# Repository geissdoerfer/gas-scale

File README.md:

# DuoClean Energy - IoT Sensor Monitoring Platform

## Project Status

✅ **Phase 1: Database Setup** - Complete
✅ **Phase 2: MQTT Ingestor** - Complete
✅ **Phase 3: Web API** - Complete
✅ **Phase 4: Web Frontend** - Complete

## What's Been Implemented

### Database (PostgreSQL + TimescaleDB)
- Complete schema with users, devices, user_device_access, sensor_readings
- TimescaleDB hypertable for sensor_readings
- Continuous aggregate for hourly statistics
- Data retention policy (1 year)
- Default admin user created
- Full init.sql script: [database/init.sql](database/init.sql)

### MQTT Ingestor Service
- MQTT client with paho-mqtt
- Database writer with connection pooling
- Auto-device registration
- Message validation
- Device ID extracted from topic (security feature)
- Error handling and logging
- Dockerized service
- Source code: [mqtt-ingestor/src/](mqtt-ingestor/src/)

### Web API (FastAPI)
- JWT authentication with access/refresh tokens
- Role-based access control (admin/user)
- User management endpoints (CRUD)
- Device management with assignment system
- Sensor reading query endpoints
- Dashboard endpoint with latest readings
- Automatic API documentation (Swagger UI)
- Source code: [web-api/src/](web-api/src/)

### Web Frontend (Vue.js 3)
- Modern responsive UI with Composition API
- User authentication and session management
- Dashboard with device cards and status indicators
- Device detail view with Chart.js visualizations
- Historical data with time-range selection
- Admin panel for user/device management
- Real-time status updates
- Source code: [frontend/src/](frontend/src/)

## Quick Start

### Prerequisites
- Docker and Docker Compose
- MQTT broker running at localhost:1883 (or adjust MQTT_BROKER_HOST in .env)

### Installation

1. **Configure environment:**
   ```bash
   # .env file already created from .env.example
   # Edit if needed:
   nano .env
   ```

2. **Start services:**
   ```bash
   docker-compose up -d
   ```

3. **View logs:**
   ```bash
   docker-compose logs -f
   ```

4. **Check status:**
   ```bash
   docker-compose ps
   ```

5. **Access the application:**
   - Frontend: http://localhost:3000
   - API Documentation: http://localhost:8000/docs
   - Database: localhost:5432

6. **Login with default admin:**
   - Username: `admin`
   - Password: `admin123`

### Testing

#### Test Database
```bash
# Access PostgreSQL
docker-compose exec postgres psql -U duoclean_user -d duoclean

# List tables
\dt

# Check admin user
SELECT * FROM users;

# Exit
\q
```

#### Test MQTT Ingestion

1. **Install mosquitto clients** (if not already installed):
   ```bash
   # Ubuntu/Debian
   sudo apt-get install mosquitto-clients

   # macOS
   brew install mosquitto
   ```

2. **Send test message:**
   ```bash
   mosquitto_pub -h localhost -t sensors/test_device_001/data -m '{
     "load": 50.5,
     "battery_voltage": 12.6,
     "temperature": 23.5
   }'
   ```

3. **Verify in database:**
   ```bash
   docker-compose exec postgres psql -U duoclean_user -d duoclean -c "SELECT * FROM sensor_readings WHERE device_id = 'test_device_001';"
   ```

4. **Check device auto-registration:**
   ```bash
   docker-compose exec postgres psql -U duoclean_user -d duoclean -c "SELECT * FROM devices WHERE device_id = 'test_device_001';"
   ```

## Project Structure

```
duocleanenergy/server/
├── docker-compose.yml          # Orchestrates all services
├── .env                        # Environment configuration
├── .env.example                # Template for environment variables
├── README.md                   # This file
│
├── docs/                       # Comprehensive documentation
│   ├── README.md              # Project overview
│   ├── ARCHITECTURE.md        # System architecture
│   ├── DATABASE.md            # Database design
│   ├── API.md                 # API documentation
│   ├── MQTT.md                # MQTT ingestor details
│   ├── FRONTEND.md            # Frontend implementation
│   ├── DEPLOYMENT.md          # Deployment guide
│   ├── IMPLEMENTATION_PHASES.md  # Step-by-step plan
│   ├── SECURITY.md            # Security considerations
│   └── TESTING.md             # Testing strategy
│
├── database/
│   └── init.sql               # Database initialization script
│
└── mqtt-ingestor/
    ├── Dockerfile
    ├── requirements.txt
    ├── .dockerignore
    └── src/
        ├── __init__.py
        ├── main.py            # Entry point
        ├── config.py          # Configuration
        ├── mqtt_client.py     # MQTT client
        └── db_writer.py       # Database writer
```

## Default Credentials

**Admin User:**
- Username: `admin`
- Password: `admin123`
- **IMPORTANT:** Change this password immediately after deployment!

## MQTT Message Format

Devices should publish JSON messages to topic: `sensors/{device_id}/data`

**Important:** The device_id is derived from the topic path, NOT from the message payload. This is more secure and prevents spoofing.

Example:
```bash
# Topic: sensors/device_001/data
# Payload:
{
  "load": 45.2,
  "battery_voltage": 12.6,
  "temperature": 23.5,
  "timestamp": "2026-01-21T10:30:00Z"
}
```

Fields:
- `load` (optional): Load reading
- `battery_voltage` (optional): Battery voltage in volts
- `temperature` (optional): Temperature in Celsius
- `timestamp` (optional): ISO 8601 timestamp (server time if omitted)

**Note:** At least one sensor value should be present in the message.

## Management Commands

```bash
# Start services
docker-compose up -d

# Stop services
docker-compose down

# View logs
docker-compose logs -f
docker-compose logs -f mqtt-ingestor  # Specific service

# Restart a service
docker-compose restart mqtt-ingestor

# Rebuild after code changes
docker-compose up -d --build

# Check resource usage
docker stats

# Clean up everything (WARNING: destroys data)
docker-compose down -v
```

## Next Steps

1. **Implement Web API (FastAPI)** - Phase 3
   - Authentication with JWT
   - User management endpoints
   - Device management endpoints
   - Sensor data query endpoints
   - See [docs/IMPLEMENTATION_PHASES.md](docs/IMPLEMENTATION_PHASES.md)

2. **Implement Web Frontend (Vue.js)** - Phase 4
   - Login page
   - Dashboard
   - Device detail views
   - Admin panel

## Documentation

Comprehensive documentation is available in the `/docs` directory:

- **[docs/README.md](docs/README.md)** - Project overview and quick start
- **[docs/ARCHITECTURE.md](docs/ARCHITECTURE.md)** - System architecture and design
- **[docs/DATABASE.md](docs/DATABASE.md)** - Database schema and queries
- **[docs/MQTT.md](docs/MQTT.md)** - MQTT ingestor implementation details
- **[docs/IMPLEMENTATION_PHASES.md](docs/IMPLEMENTATION_PHASES.md)** - Detailed implementation plan
- **[docs/DEPLOYMENT.md](docs/DEPLOYMENT.md)** - Deployment and operations guide
- **[docs/SECURITY.md](docs/SECURITY.md)** - Security best practices
- **[docs/TESTING.md](docs/TESTING.md)** - Testing strategy

## Troubleshooting

### Services won't start
```bash
# Check logs
docker-compose logs

# Check if ports are available
sudo lsof -i :5432
sudo lsof -i :1883
```

### MQTT ingestor can't connect to broker
```bash
# Verify MQTT broker is running
sudo systemctl status mosquitto

# Test MQTT connection
mosquitto_sub -h localhost -t '#' -v

# Check MQTT_BROKER_HOST in .env
# Should be "host.docker.internal" to access host's localhost from Docker
```

### Database connection failed
```bash
# Check if postgres is healthy
docker-compose ps postgres

# Verify credentials
docker-compose exec postgres psql -U duoclean_user -d duoclean
```

### Messages not appearing in database
```bash
# Check ingestor logs
docker-compose logs -f mqtt-ingestor

# Verify message format
# Ensure device_id in payload matches device_id in topic
```

## Support

For detailed information, refer to:
- Implementation guide: [docs/IMPLEMENTATION_PHASES.md](docs/IMPLEMENTATION_PHASES.md)
- Troubleshooting: [docs/DEPLOYMENT.md](docs/DEPLOYMENT.md#troubleshooting)
- Architecture details: [docs/ARCHITECTURE.md](docs/ARCHITECTURE.md)

## License

[Your License Here]

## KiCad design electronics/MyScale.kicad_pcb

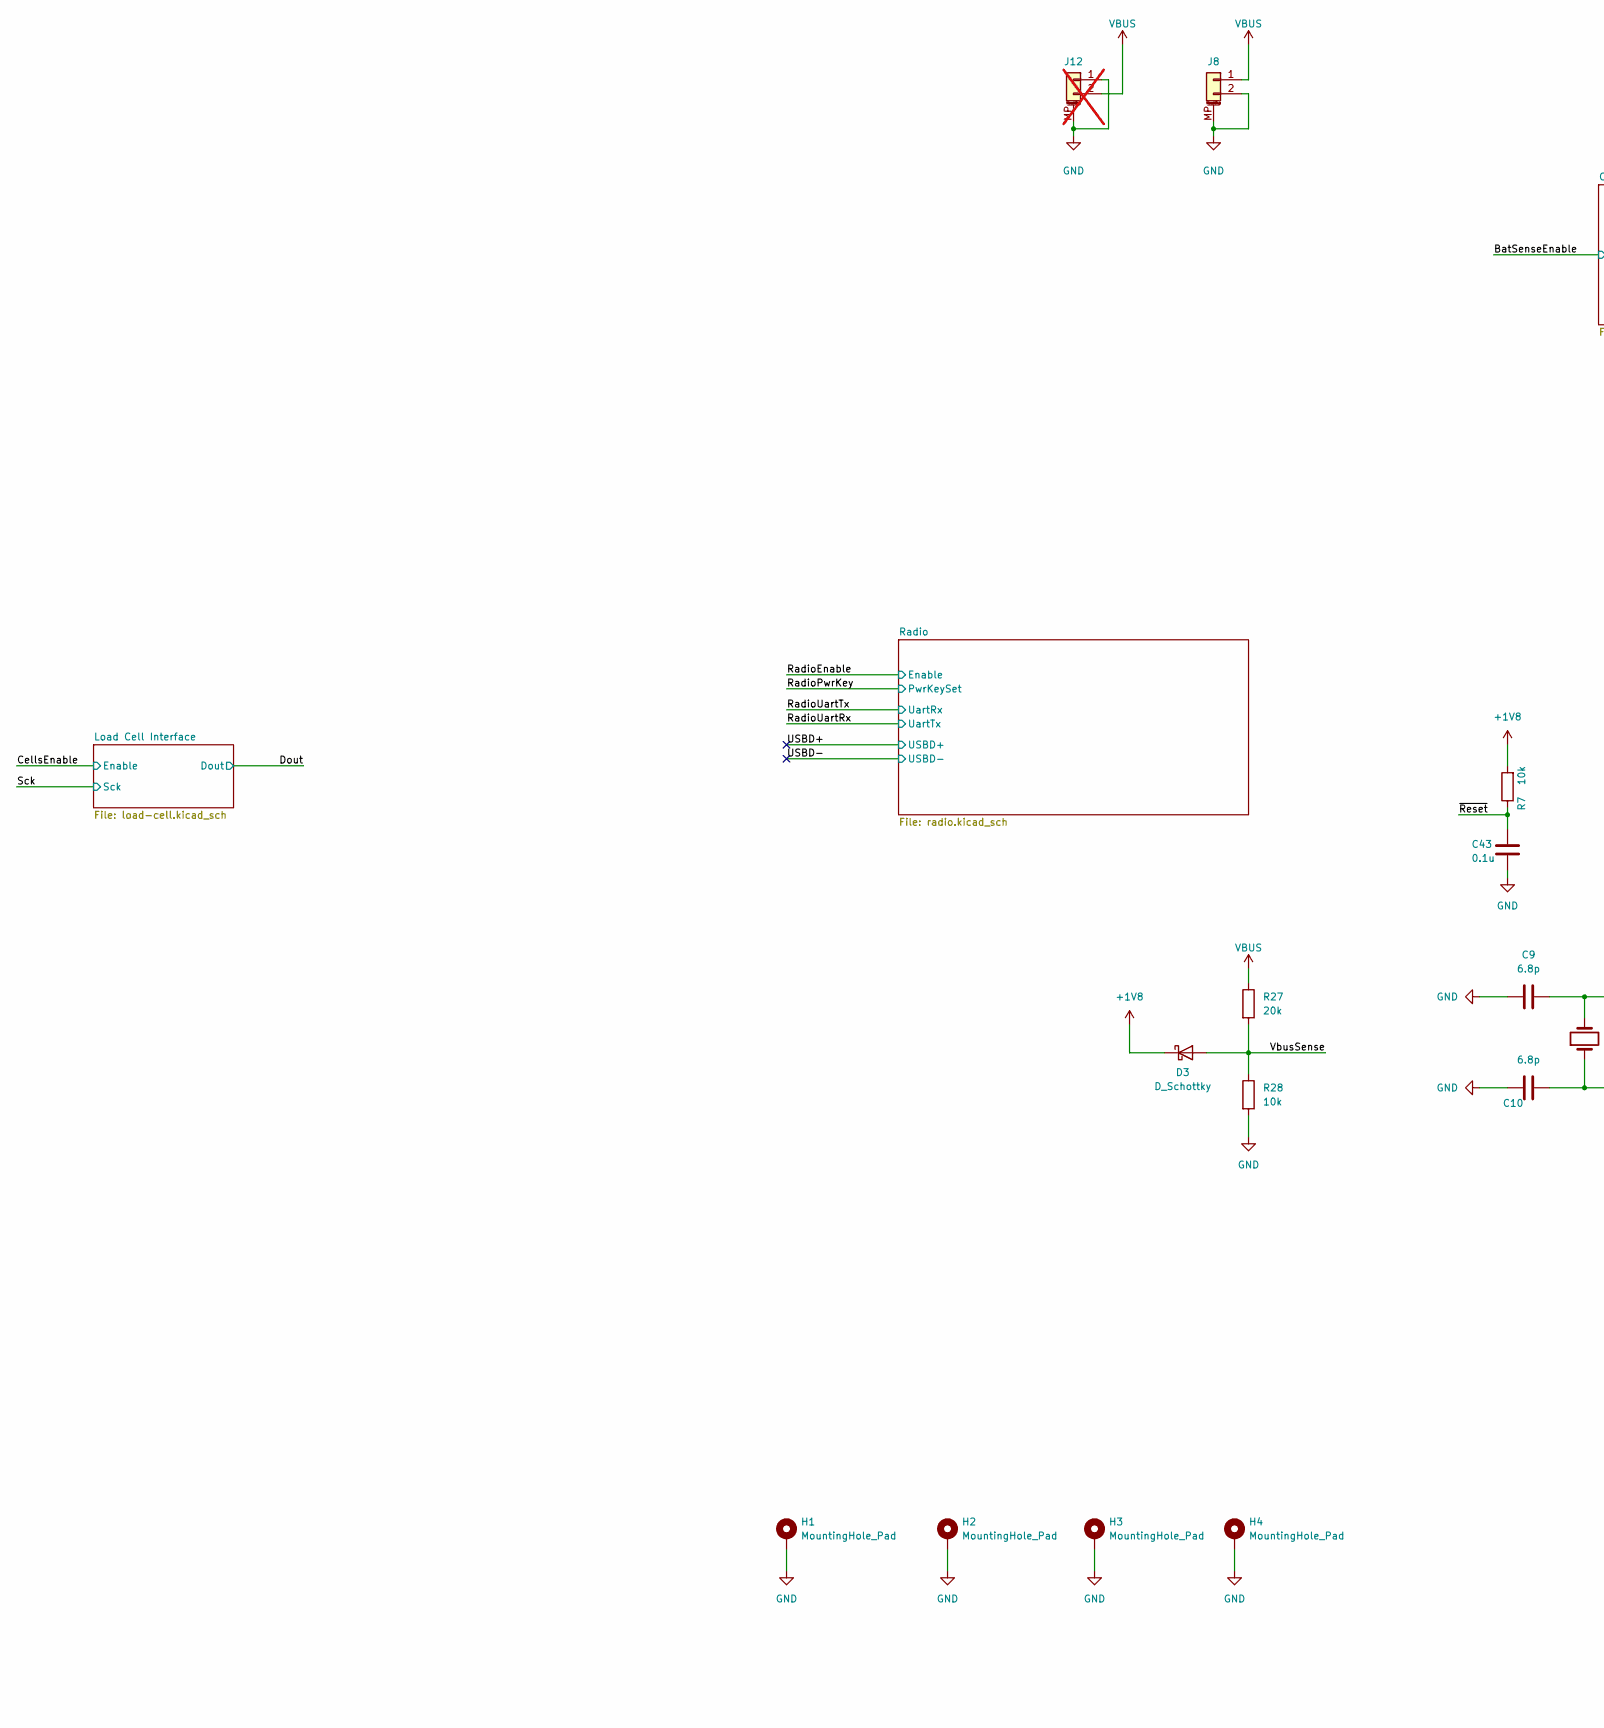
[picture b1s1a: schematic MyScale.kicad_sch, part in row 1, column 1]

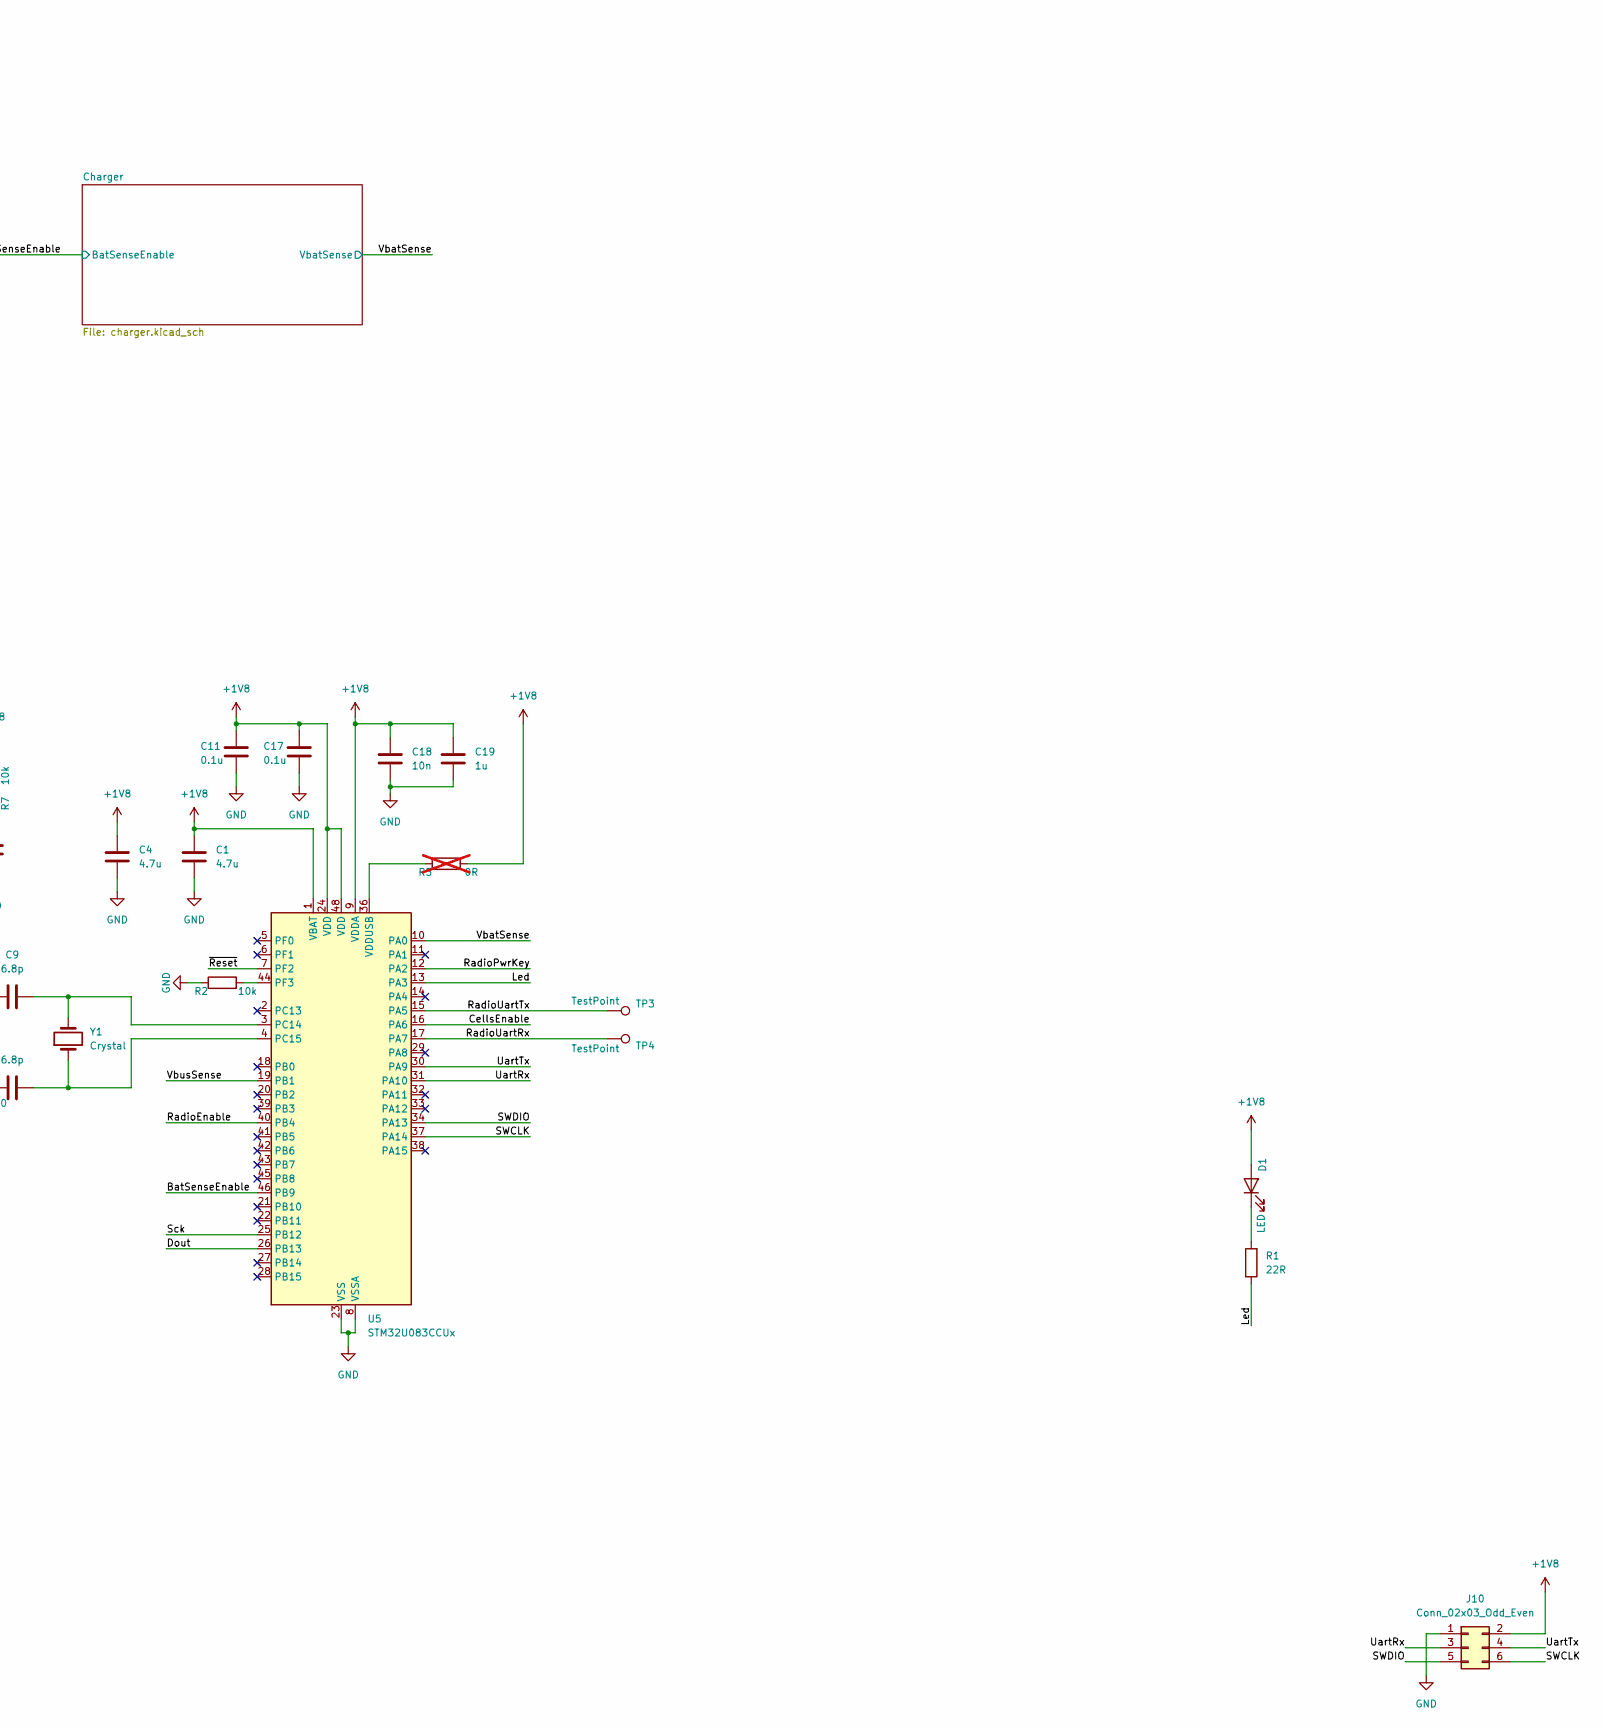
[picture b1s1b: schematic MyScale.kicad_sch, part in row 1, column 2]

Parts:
C1, C4: 4.7u; C_0603_1608Metric
C9, C10: 6.8p; C_0603_1608Metric
C11, C17, C43: 0.1u; C_0603_1608Metric
C18: 10n; C_0603_1608Metric
C19: 1u; C_0603_1608Metric
D1: LED; LED_0603_1608Metric; MPN YLED0603O
D3: D_Schottky; D_SOD-523; MPN BAT30KFILM
H1, H2, H3, H4: MountingHole_Pad; MountingHole_3.2mm_M3_Pad
J8: Conn_01x02_MountingPin; JST_S2B-PH-SM4-TB(LF)(SN); MPN S2B-PH-SM4-TB(LF)(SN)
J10: Conn_02x03_Odd_Even; Tag-Connect_TC2030-IDC-NL_2x03_P1.27mm_Vertical
J12: Conn_01x02_MountingPin; JST_S2B-PH-SM4-TB(LF)(SN); MPN S2B-PH-SM4-TB(LF)(SN); not fitted
R1: 22R; R_0603_1608Metric
R2, R7, R28: 10k; R_0603_1608Metric
R5: 0R; R_0603_1608Metric; not fitted
R27: 20k; R_0603_1608Metric
TP3, TP4: TestPoint; TestPoint_Pad_D1.0mm
U5: STM32U083CCUx; QFN-48-1EP_7x7mm_P0.5mm_EP5.6x5.6mm; MPN STM32U083CCU6
Y1: Crystal; Crystal_SMD_2012-2Pin_2.0x1.2mm; MPN NX2012SA-32.768KHZ-EXS00A-MU00527

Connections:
+1V8: C1.1, C4.1, C11.1, C17.1, C18.1, C19.1, D1.2 (A), D3.1 (K), J10.2, R5.2, R7.2, U5.1 (VBAT), U5.9 (VDDA), U5.24 (VDD), U5.48 (VDD); also elsewhere on the board
/BatSenseEnable: U5.46 (PB9); also elsewhere on the board
/CellsEnable: U5.16 (PA6); also elsewhere on the board
/Dout: U5.26 (PB13); also elsewhere on the board
/Led: R1.1, U5.13 (PA3)
/RadioEnable: U5.40 (PB4); also elsewhere on the board
/RadioPwrKey: U5.12 (PA2); also elsewhere on the board
/RadioUartRx: TP4.1 (1_1), U5.17 (PA7); also elsewhere on the board
/RadioUartTx: TP3.1 (1_1), U5.15 (PA5); also elsewhere on the board
/SWCLK: J10.6, U5.37 (PA14)
/SWDIO: J10.5, U5.34 (PA13)
/Sck: U5.25 (PB12); also elsewhere on the board
/UartRx: J10.3, U5.31 (PA10)
/UartTx: J10.4, U5.30 (PA9)
/VbatSense: U5.10 (PA0); also elsewhere on the board
/VbusSense: D3.2 (A), R27.2, R28.1, U5.19 (PB1)
/~Reset: C43.1, R7.1, U5.7 (PF2)
GND: C1.2, C4.2, C9.1, C10.1, C11.2, C17.2, C18.2, C19.2, C43.2, H1.1 (1_1), H2.1 (1_1), H3.1 (1_1), H4.1 (1_1), J8.2, J8.MP (MountPin), J10.1, J12.1, J12.MP (MountPin), R2.1, R28.2, U5.8 (VSSA), U5.23 (VSS), U5.35 (VSS), U5.47 (VSS), U5.49 (VSS); also elsewhere on the board
unnamed: D1.1 (K), R1.2
unnamed: C9.2, U5.3 (PC14), Y1.2
unnamed: C10.2, U5.4 (PC15), Y1.1
unnamed: R2.2, U5.44 (PF3)
unnamed: R5.1, U5.36 (VDDUSB)
VBUS: J8.1, J12.2, R27.1; also elsewhere on the board

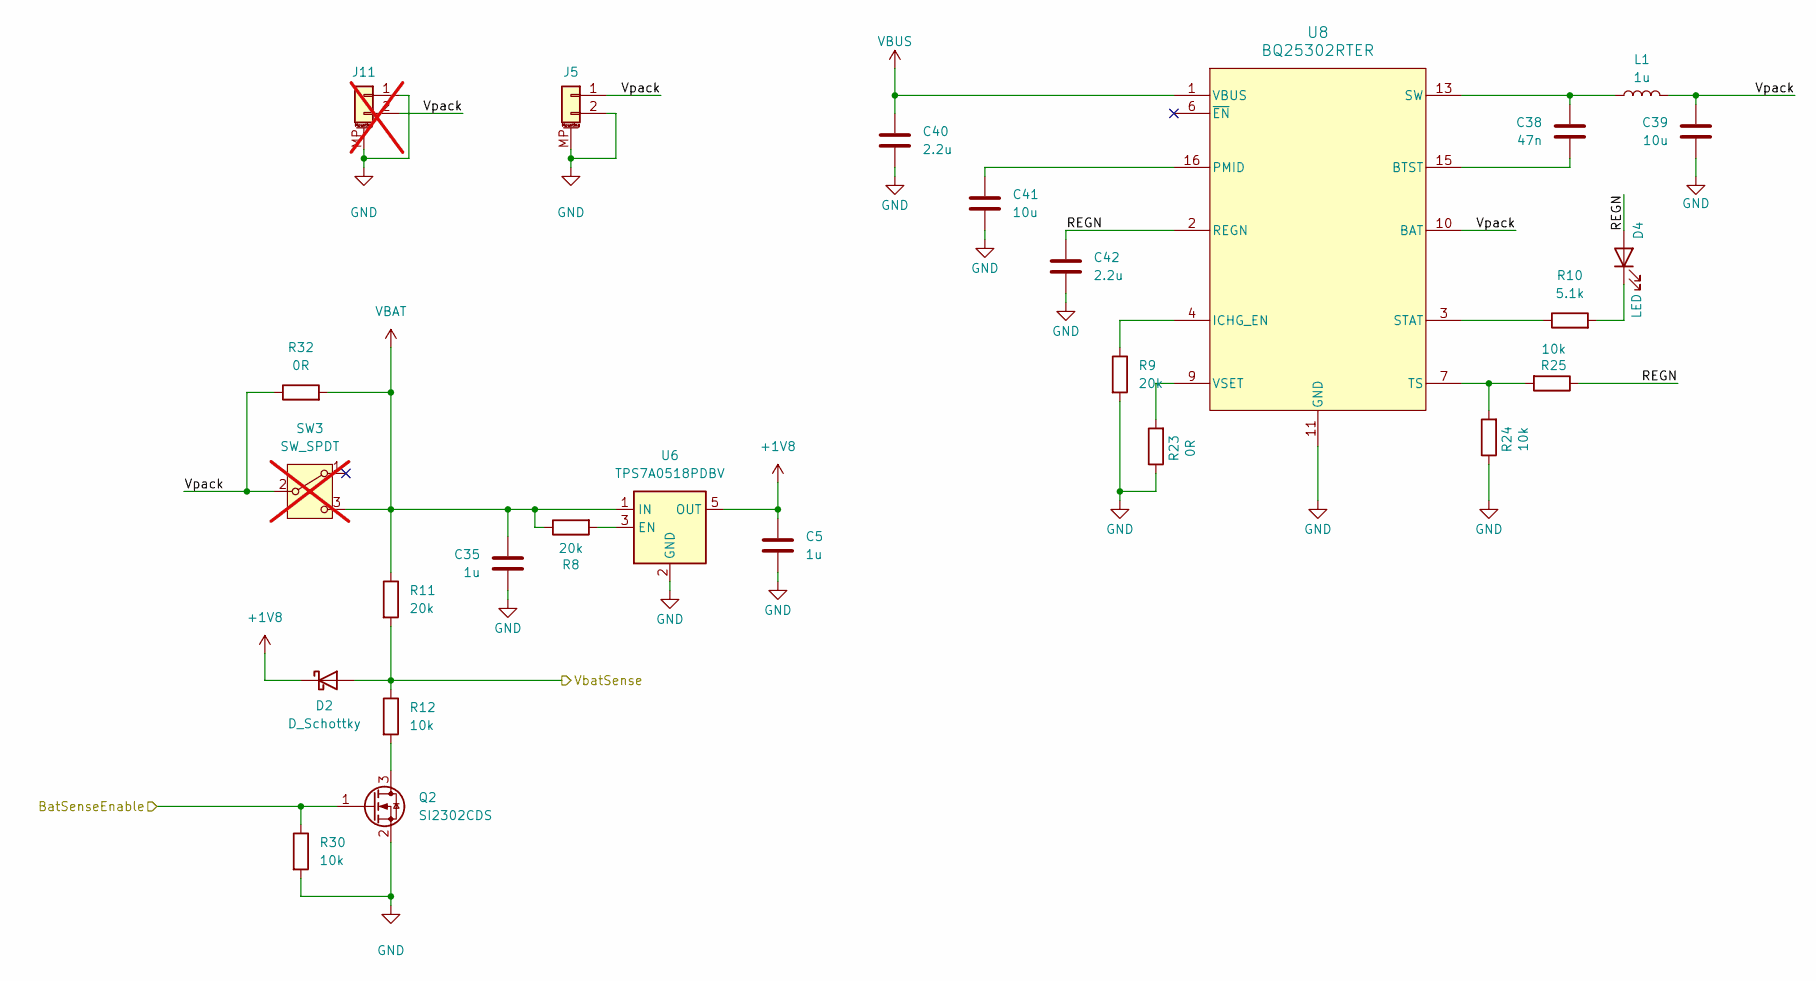
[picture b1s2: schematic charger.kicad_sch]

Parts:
C5, C35: 1u; C_0603_1608Metric
C38: 47n; C_0603_1608Metric
C39, C41: 10u; C_0805_2012Metric
C40, C42: 2.2u; C_0603_1608Metric
D2: D_Schottky; D_SOD-523; MPN BAT30KFILM
D4: LED; LED_0603_1608Metric; MPN YLED0603O
J5: Conn_01x02_MountingPin; JST_S2B-PH-SM4-TB(LF)(SN); MPN S2B-PH-SM4-TB(LF)(SN)
J11: Conn_01x02_MountingPin; JST_S2B-PH-SM4-TB(LF)(SN); MPN S2B-PH-SM4-TB(LF)(SN); not fitted
L1: 1u; MG_MAPM0420F; MPN MAPM0420LA1R0M-LF
Q2: SI2302CDS; SOT-23-3; MPN SI2302CDS-T1-GE3
R8, R9, R11: 20k; R_0603_1608Metric
R10: 5.1k; R_0603_1608Metric
R12, R24, R25, R30: 10k; R_0603_1608Metric
R23: 0R; R_0603_1608Metric
R32: 0R; R_1206_3216Metric
SW3: SW_SPDT; NKK_CS12ANW03; MPN AYZ0102AURLC; not fitted
U6: TPS7A0518PDBV; SOT-23-5; MPN TPS7A0518PDBV
U8: BQ25302RTER; TI_RTE0016C; MPN BQ25302RTER

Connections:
+1V8: C5.1, D2.1 (K), U6.5 (OUT); also elsewhere on the board
/BatSenseEnable: Q2.1 (G), R30.1; also elsewhere on the board
/Charger/REGN: C42.1, D4.2 (A), R25.1, U8.2 (REGN)
/Charger/Vpack: C39.1, J5.1, J11.2, L1.2, R32.1, SW3.2 (B), U8.10 (BAT)
/VbatSense: D2.2 (A), R11.2, R12.1; also elsewhere on the board
GND: C5.2, C35.2, C39.2, C40.2, C41.2, C42.2, J5.2, J5.MP (MountPin), J11.1, J11.MP (MountPin), Q2.2 (S), R9.2, R23.1, R24.1, R30.2, U6.2 (GND), U8.11 (GND), U8.12 (GND), U8.17 (PAD); also elsewhere on the board
unnamed: C38.1, L1.1, U8.13 (SW), U8.14 (SW)
unnamed: D4.1 (K), R10.2
unnamed: Q2.3 (D), R12.2
unnamed: R8.2, U6.3 (EN)
unnamed: C38.2, U8.15 (BTST)
unnamed: R9.1, U8.4 (ICHG_EN)
unnamed: C41.1, U8.16 (PMID)
unnamed: R10.1, U8.3 (STAT)
unnamed: R24.2, R25.2, U8.7 (TS)
unnamed: R23.2, U8.9 (VSET)
VBAT: C35.1, R8.1, R11.1, R32.2, SW3.3 (C), U6.1 (IN); also elsewhere on the board
VBUS: C40.1, U8.1 (VBUS); also elsewhere on the board

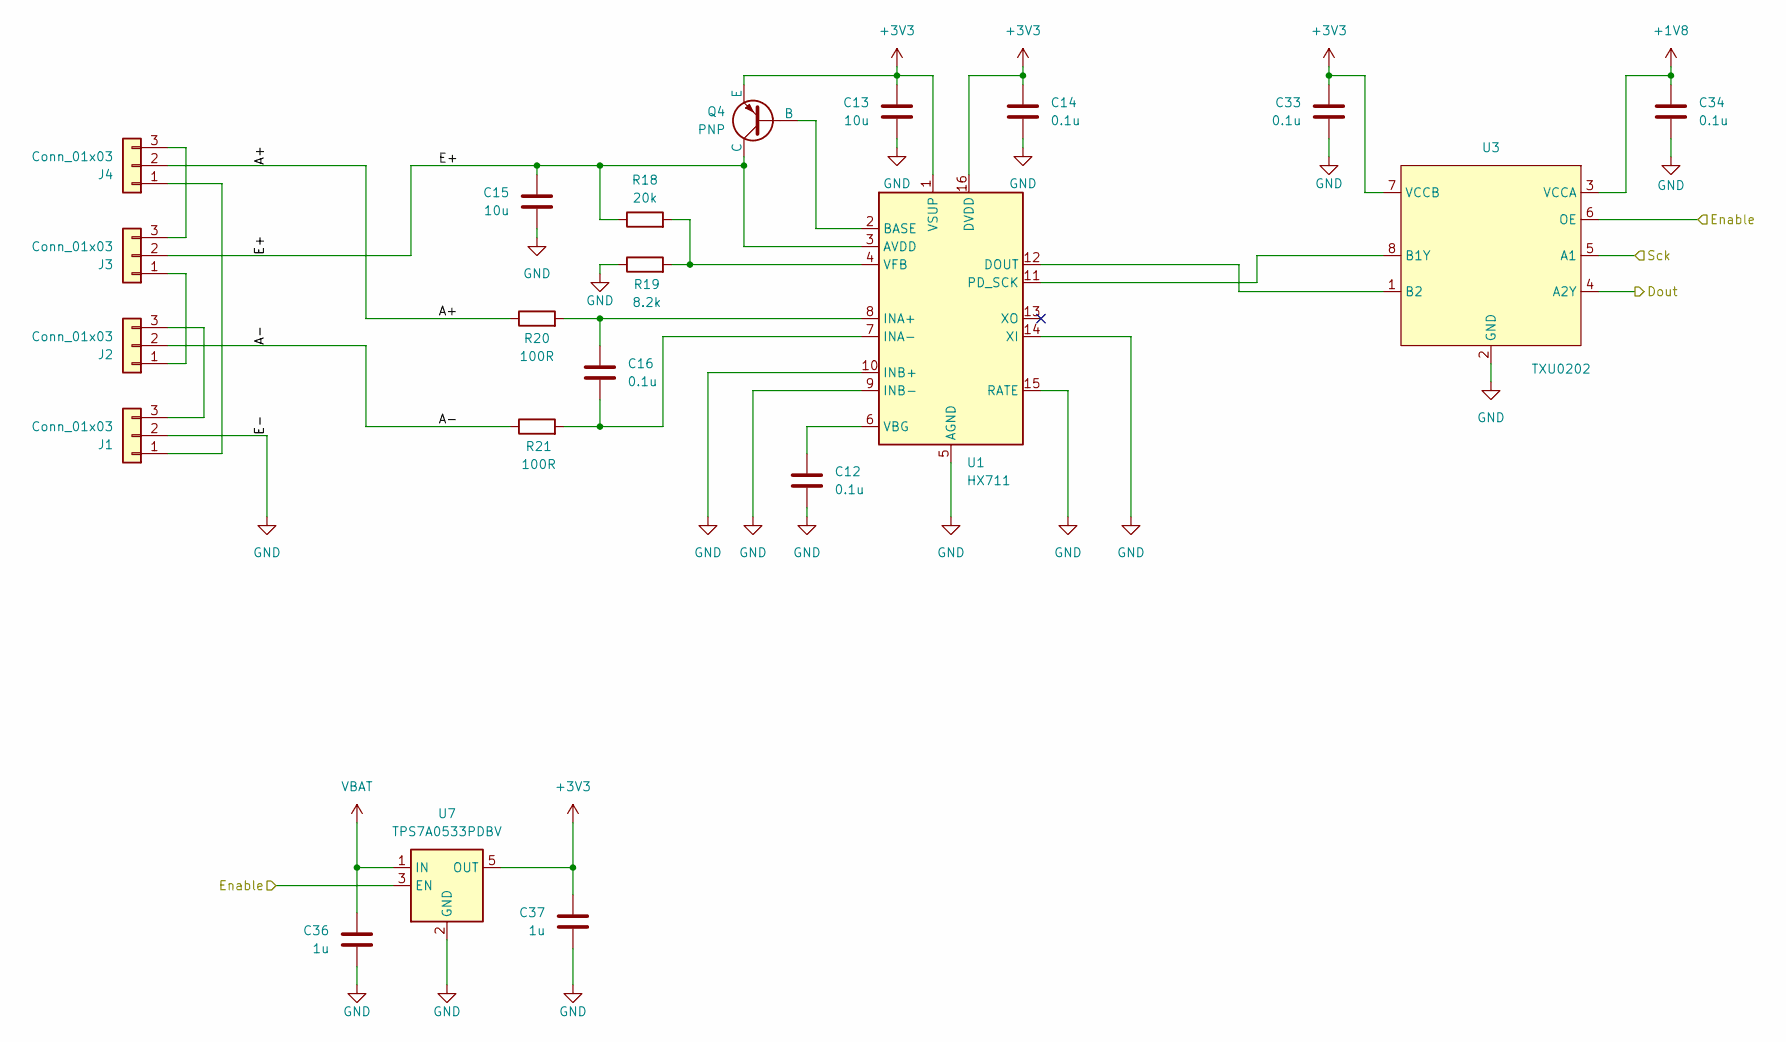
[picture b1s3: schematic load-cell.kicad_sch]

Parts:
C12, C14, C16, C33, C34: 0.1u; C_0603_1608Metric
C13, C15: 10u; C_0805_2012Metric
C36, C37: 1u; C_0603_1608Metric
J1, J2, J3, J4: Conn_01x03; LoadCellPads
Q4: PNP; SOT-23; MPN MMBT4403
R18: 20k; R_0603_1608Metric
R19: 8.2k; R_0603_1608Metric
R20, R21: 100R; R_0603_1608Metric
U1: HX711; SOIC-16_3.9x9.9mm_P1.27mm; MPN HX711
U3: TXU0202; VSSOP-8_2.3x2mm_P0.5mm; MPN TXU0202DCUR
U7: TPS7A0533PDBV; SOT-23-5; MPN TPS7A0533PDBV

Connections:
+1V8: C34.1, U3.3 (VCCA); also elsewhere on the board
+3V3: C13.1, C14.1, C33.1, C37.1, Q4.3 (E), U1.1 (VSUP), U1.16 (DVDD), U3.7 (VCCB), U7.5 (OUT)
/CellsEnable: U3.6 (OE), U7.3 (EN); also elsewhere on the board
/Dout: U3.4 (A2Y); also elsewhere on the board
/Load Cell Interface/A+: J4.2, R20.1
/Load Cell Interface/A-: J2.2, R21.1
/Load Cell Interface/E+: C15.1, J3.2, Q4.1 (C), R18.1, U1.3 (AVDD)
/Sck: U3.5 (A1); also elsewhere on the board
GND: C12.2, C13.2, C14.2, C15.2, C33.2, C34.2, C36.2, C37.2, J1.2, R19.1, U1.5 (AGND), U1.9 (INB-), U1.10 (INB+), U1.14 (XI), U1.15 (RATE), U3.2 (GND), U7.2 (GND); also elsewhere on the board
unnamed: J1.1, J4.1
unnamed: J1.3, J2.3
unnamed: J2.1, J3.1
unnamed: J3.3, J4.3
unnamed: Q4.2 (B), U1.2 (BASE)
unnamed: U1.12 (DOUT), U3.1 (B2)
unnamed: C16.1, R20.2, U1.8 (INA+)
unnamed: C16.2, R21.2, U1.7 (INA-)
unnamed: U1.11 (PD_SCK), U3.8 (B1Y)
unnamed: C12.1, U1.6 (VBG)
unnamed: R18.2, R19.2, U1.4 (VFB)
VBAT: C36.1, U7.1 (IN); also elsewhere on the board

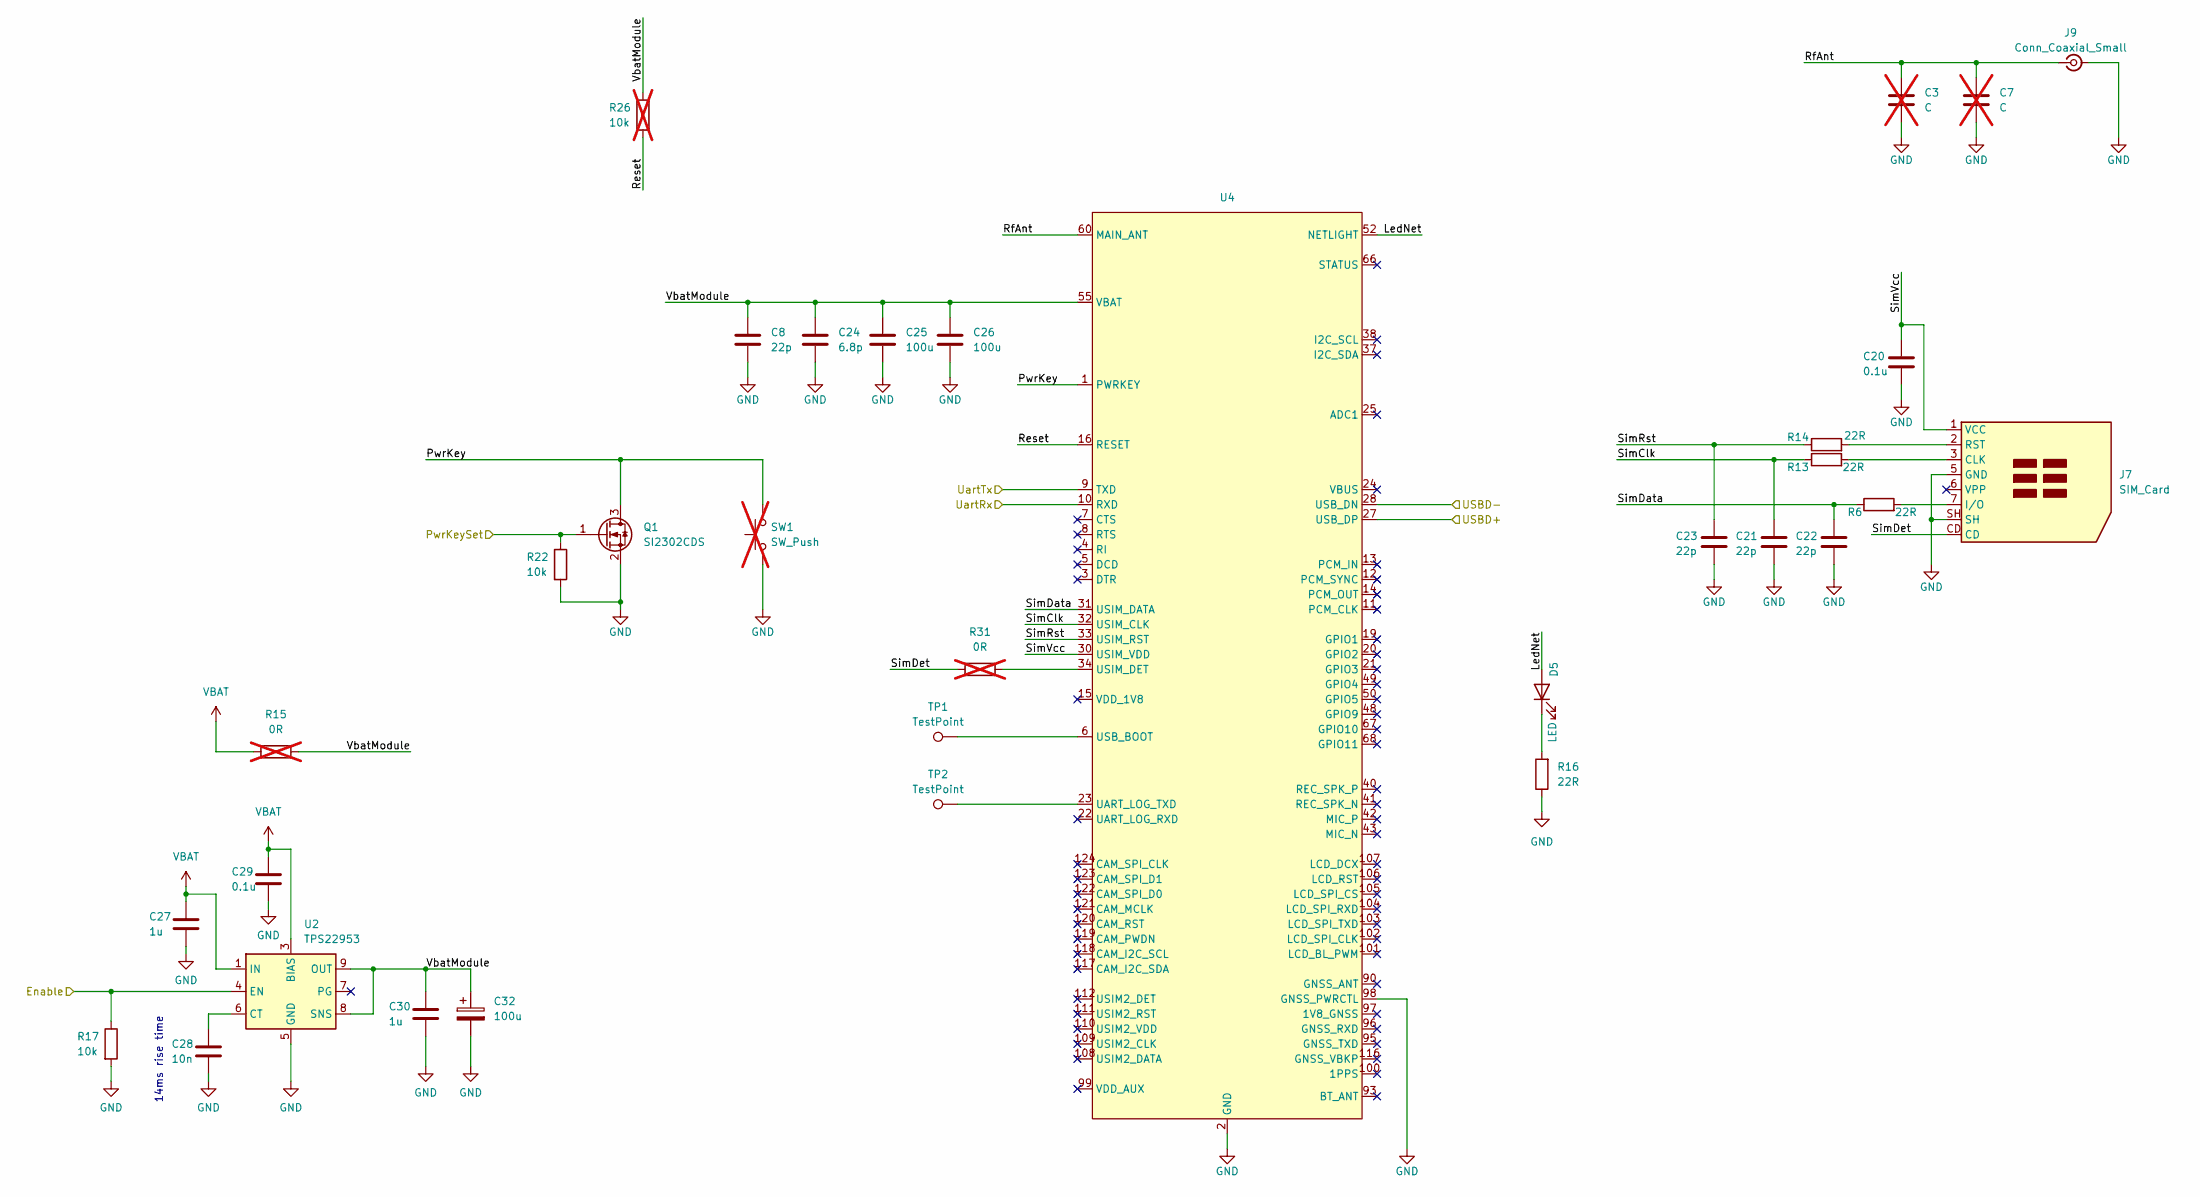
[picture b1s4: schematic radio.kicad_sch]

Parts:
C3, C7: C; C_0402_1005Metric; not fitted
C8, C21, C22, C23: 22p; C_0603_1608Metric
C20, C29: 0.1u; C_0603_1608Metric
C24: 6.8p; C_0603_1608Metric
C25, C26: 100u; C_1210_3225Metric; MPN TPSB107K006R0250
C27, C30: 1u; C_0603_1608Metric
C28: 10n; C_0603_1608Metric
C32: 100u; CP_Elec_6.3x7.7; MPN RSA1E101MCN1GS
D5: LED; LED_0603_1608Metric; MPN YLED0603O
J7: SIM_Card; nanoSIM_Hinged_CUI_NSIM-2-C; MPN NSIM-2-C
J9: Conn_Coaxial_Small; U.FL_Hirose_U.FL-R-SMT-1_Vertical; MPN U.FL-R-SMT-1(01)
Q1: SI2302CDS; SOT-23-3; MPN SI2302CDS-T1-GE3
R6, R13, R14, R16: 22R; R_0603_1608Metric
R15: 0R; R_1206_3216Metric; not fitted
R17, R22: 10k; R_0603_1608Metric
R26: 10k; R_0603_1608Metric; not fitted
R31: 0R; R_0603_1608Metric; not fitted
SW1: SW_Push; SW_SPST_TL3305A; MPN TL3305AF160QG; not fitted
TP1, TP2: TestPoint; TestPoint_Pad_D1.0mm
U2: TPS22953; TI_DQC0010A; MPN TPS22953DQCR
U4: A7670_STAMP; MPN A7670E-LASE

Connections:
/Radio/LedNet: D5.2 (A), U4.52 (NETLIGHT)
/Radio/PwrKey: Q1.3 (D), SW1.2, U4.1 (PWRKEY)
/Radio/Reset: R26.2, U4.16 (RESET)
/Radio/RfAnt: C3.1, C7.1, J9.1 (In), U4.60 (MAIN_ANT)
/Radio/SimClk: C21.1, R13.1, U4.32 (USIM_CLK)
/Radio/SimData: C22.1, R6.1, U4.31 (USIM_DATA)
/Radio/SimDet: J7.CD, R31.2
/Radio/SimRst: C23.1, R14.1, U4.33 (USIM_RST)
/Radio/SimVcc: C20.1, J7.1 (VCC), U4.30 (USIM_VDD)
/Radio/VbatModule: C8.1, C24.1, C25.1, C26.1, C30.1, C32.1, R15.2, R26.1, U2.8 (SNS), U2.9 (OUT), U2.10 (OUT), U4.55 (VBAT), U4.56 (VBAT), U4.57 (VBAT)
/RadioEnable: R17.1, U2.4 (EN); also elsewhere on the board
/RadioPwrKey: Q1.1 (G), R22.1; also elsewhere on the board
/RadioUartRx: U4.9 (TXD); also elsewhere on the board
/RadioUartTx: U4.10 (RXD); also elsewhere on the board
/USBD+: U4.27 (USB_DP)
/USBD-: U4.28 (USB_DN)
GND: C3.2, C7.2, C8.2, C20.2, C21.2, C22.2, C23.2, C24.2, C25.2, C26.2, C27.2, C28.2, C29.2, C30.2, C32.2, J7.5 (GND), J7.SH, J9.2 (Ext), Q1.2 (S), R16.1, R17.2, R22.2, SW1.1, U2.5 (GND), U2.11 (PAD), U4.2 (GND), U4.17 (GND), U4.18 (GND), U4.29 (GND), U4.39 (GND), U4.45 (GND), U4.46 (GND), U4.54 (GND), U4.58 (GND), U4.59 (GND), U4.61 (GND), U4.62 (GND), U4.63 (GND), U4.64 (GND), U4.65 (GND), U4.69 (GND), U4.70 (GND), U4.71 (GND), U4.72 (GND), U4.73 (GND), U4.74 (GND), U4.75 (GND), U4.76 (GND), U4.77 (GND), U4.78 (GND), U4.79 (GND), U4.80 (GND), U4.81 (GND), U4.82 (GND), U4.83 (GND), U4.84 (GND), U4.85 (GND), U4.86 (GND), U4.87 (GND), U4.88 (GND), U4.89 (GND), U4.91 (GND), U4.92 (GND), U4.94 (GND), U4.98 (GNSS_PWRCTL); also elsewhere on the board
unnamed: D5.1 (K), R16.2
unnamed: J7.3 (CLK), R13.2
unnamed: J7.7 (I/O), R6.2
unnamed: J7.2 (RST), R14.2
unnamed: C28.1, U2.6 (CT)
unnamed: TP2.1 (1_1), U4.23 (UART_LOG_TXD)
unnamed: TP1.1 (1_1), U4.6 (USB_BOOT)
unnamed: R31.1, U4.34 (USIM_DET)
VBAT: C27.1, C29.1, R15.1, U2.1 (IN), U2.2 (IN), U2.3 (BIAS); also elsewhere on the board

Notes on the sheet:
14ms rise time

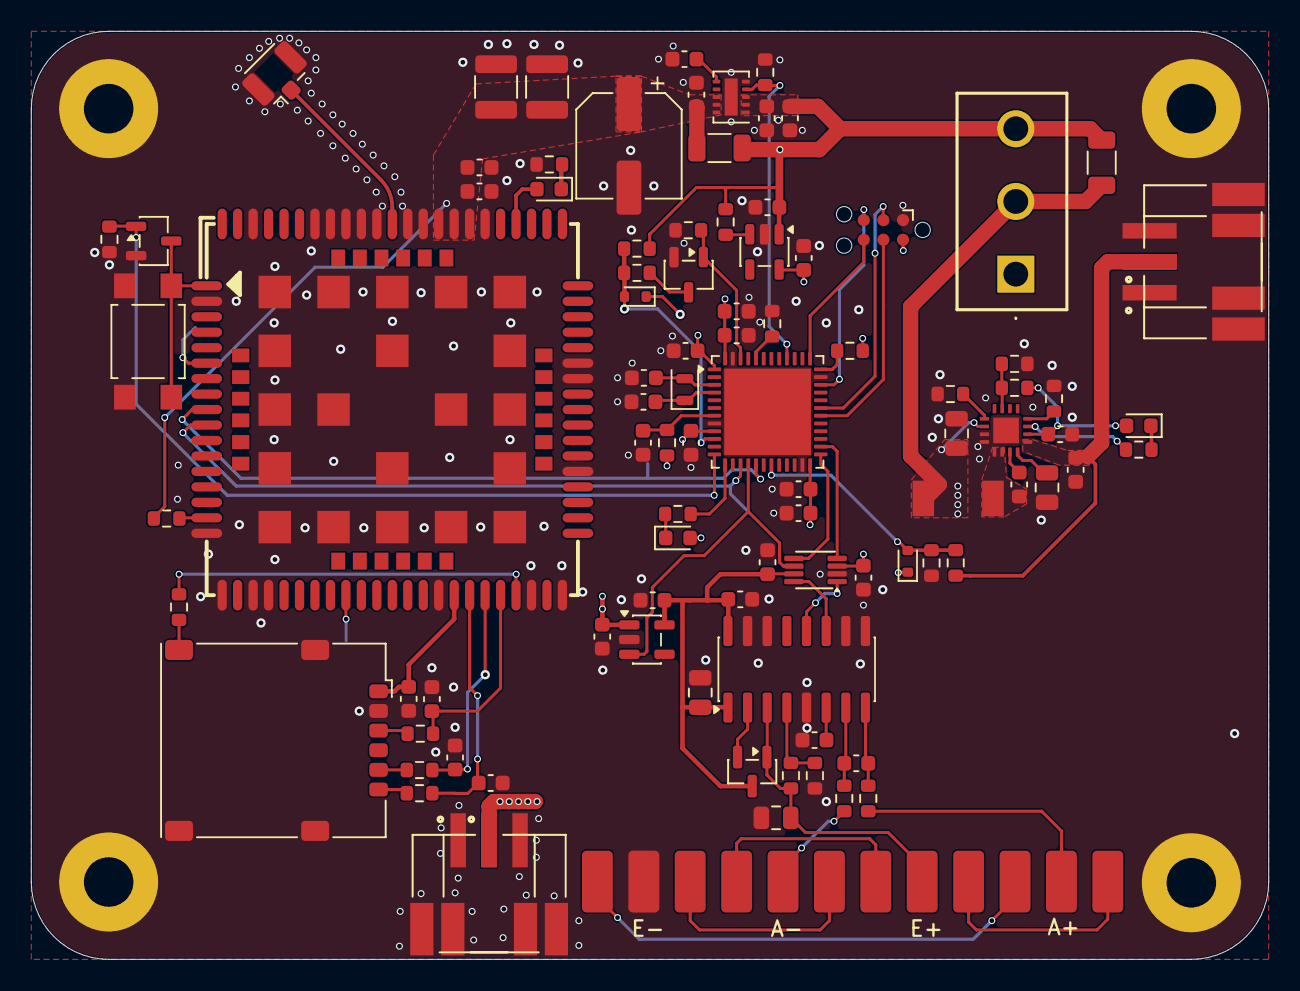
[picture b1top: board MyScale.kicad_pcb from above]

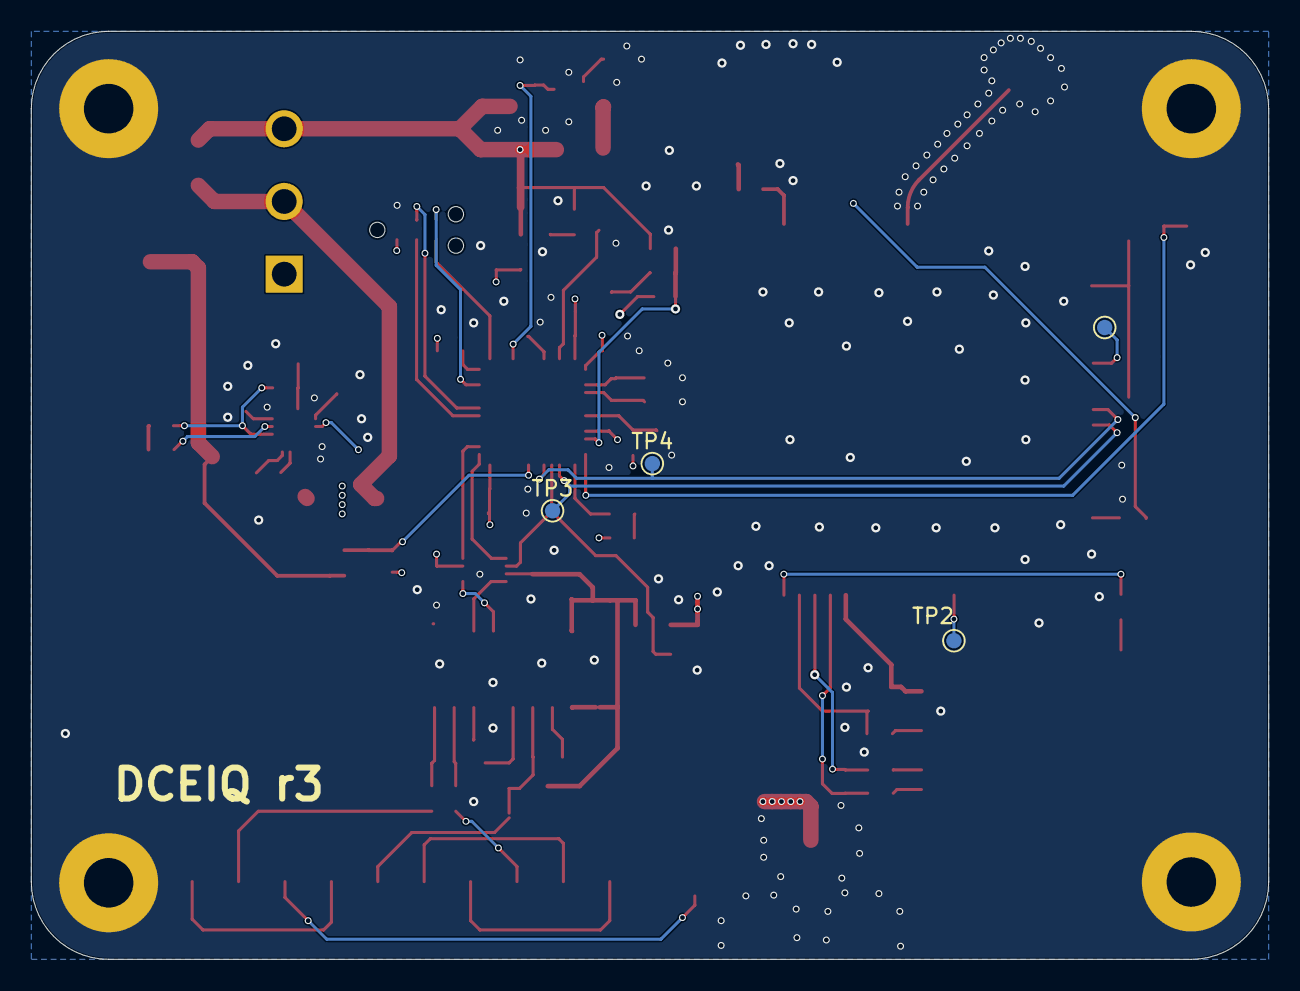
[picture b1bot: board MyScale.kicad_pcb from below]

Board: 4 copper layers, 80.0 x 60.0 mm, 106 parts (4 on the bottom side), 70 nets.
